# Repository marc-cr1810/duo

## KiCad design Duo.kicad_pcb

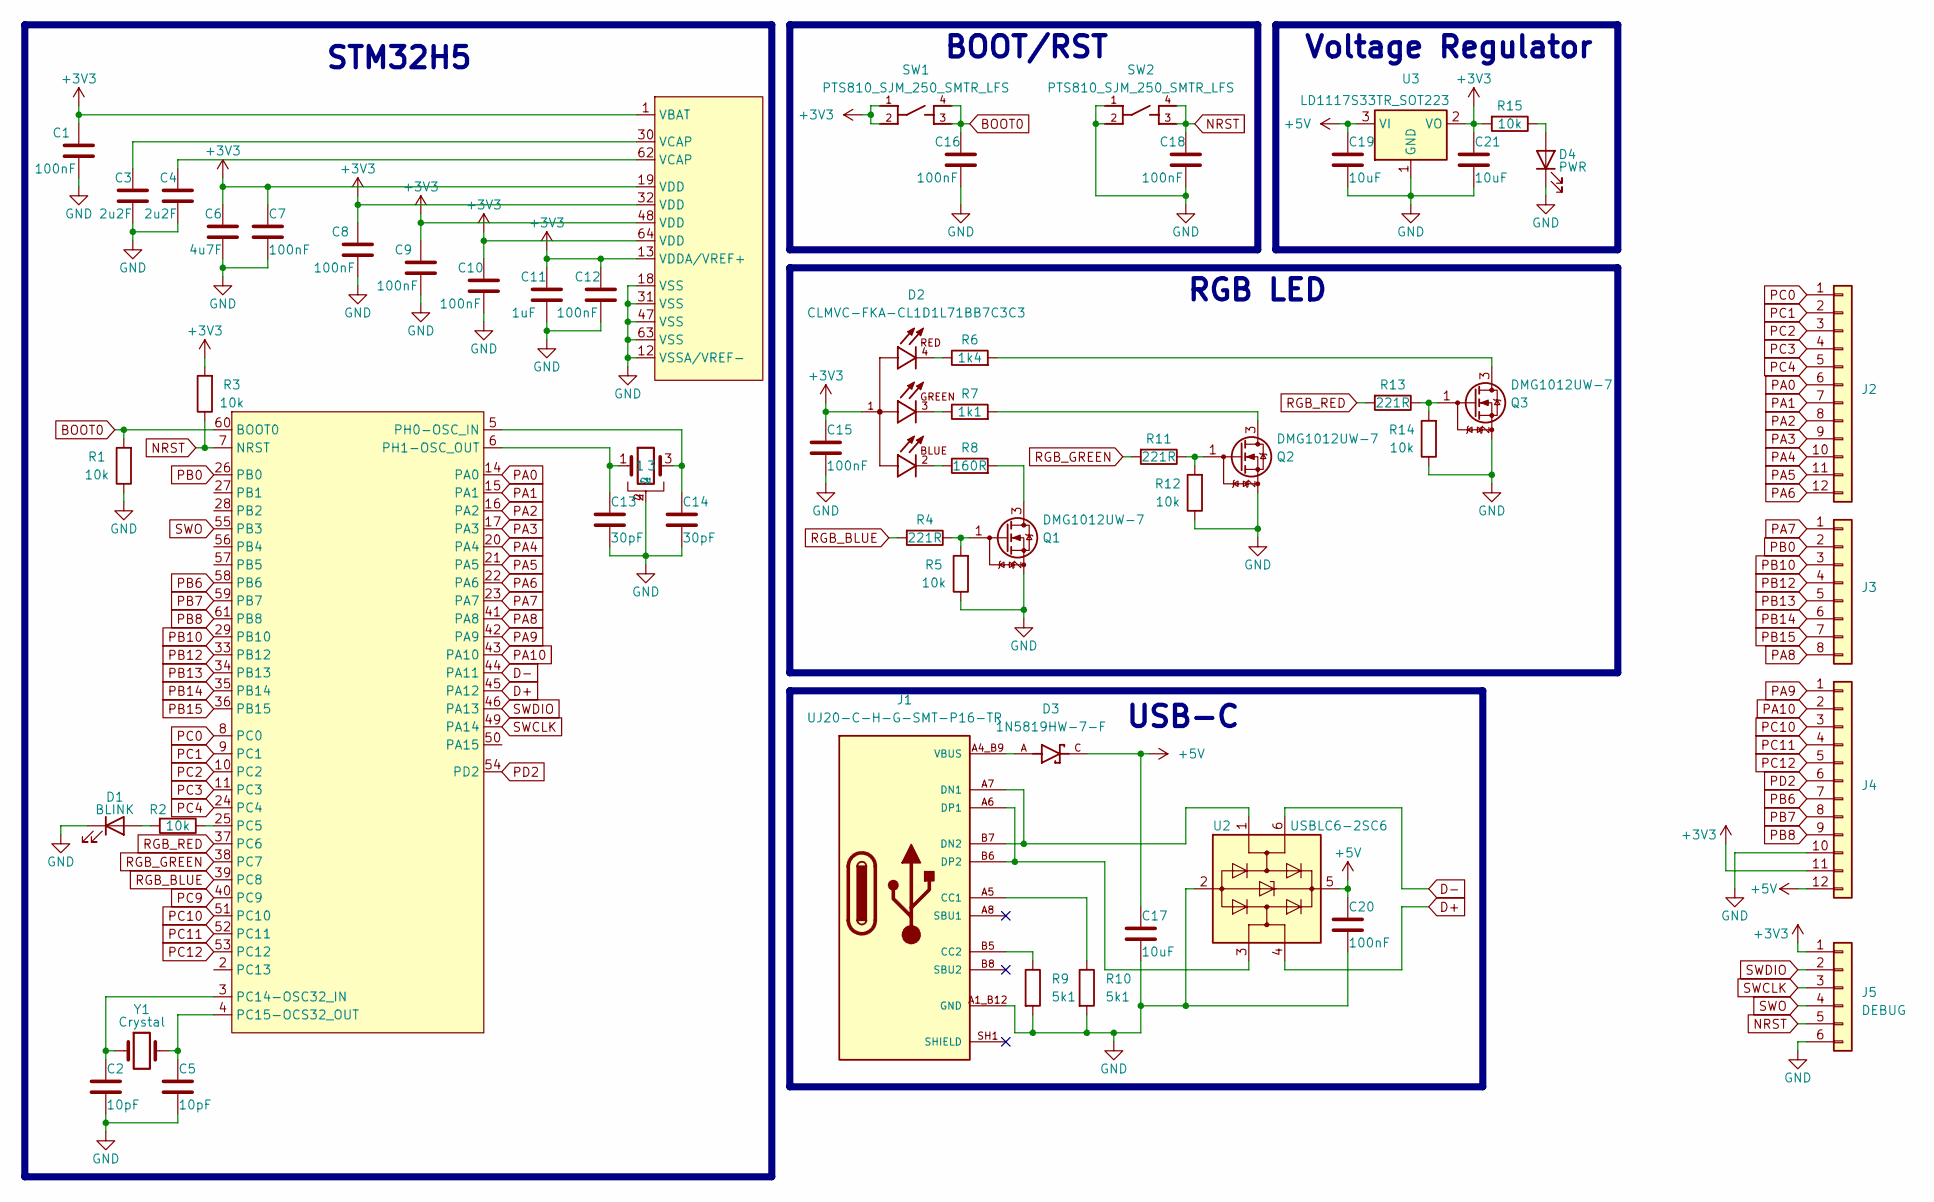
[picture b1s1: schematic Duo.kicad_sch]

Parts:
C1, C7, C8, C9, C10, C12, C15, C16, C18, C20: 100nF; C_0402_1005Metric; Part Number CL05B104KA5NNNC
C2, C5: 10pF; C_0402_1005Metric; Part Number CC0402JRNPO9BN100
C3, C4: 2u2F; C_0603_1608Metric; Part Number CL10A225KO8NNNC
C6: 4u7F; C_0603_1608Metric; Part Number CL10A475KO8NNNC
C11: 1uF; C_0402_1005Metric; Part Number GRM155R61E105KA12D
C13, C14: 30pF; C_0402_1005Metric; Part Number CC0402JRNPO9BN300
C17, C19, C21: 10uF; C_0603_1608Metric; Part Number CL10A106KP8NNNC
D1: BLINK; LED_0603_1608Metric
D2: CLMVC-FKA-CL1D1L71BB7C3C3; LED_CLMVC-FKA-CL1D1L71BB7C3C3; PARTREV 14; DigiKey_Part_Number CLMVC-FKA-CL1D1L71BB7C3C3CT-ND
D3: 1N5819HW-7-F; SOD3715X145N; Part Number 1N5819HW-7-F
D4: PWR; LED_0603_1608Metric
J1: UJ20-C-H-G-SMT-P16-TR; SAMESKY_UJ20-C-H-G-SMT-P16-TR; PARTREV 1.0; DigiKey_Part_Number 2223-UJ20-C-H-G-SMT-P16-TRCT-ND
J2, J4: PinHeader-Castellated-12
J3: PinHeader-Castellated-8
J5: DEBUG; PinHeader_1x06_P2.54mm_Vertical
Q1, Q2, Q3: DMG1012UW-7; SOT-323_SC-70; Part Number DMG1012UW-7
R1, R2, R3, R5, R12, R14, R15: 10k; R_0402_1005Metric; Part Number AC0402FR-0710KL
R4, R11, R13: 221R; R_0402_1005Metric; Part Number RC0402FR-07221RL
R6: 1k4; R_0402_1005Metric; Part Number RC0402FR-071K4L
R7: 1k1; R_0402_1005Metric; Part Number RC0402FR-071K1L
R8: 160R; R_0402_1005Metric; Part Number RC0402FR-07160RL
R9, R10: 5k1; R_0402_1005Metric; Part Number RC0402FR-075K1L
SW1, SW2: PTS810_SJM_250_SMTR_LFS; SW_PTS810_SJM_250_SMTR_LFS; Part Number PTS810SJG250SMTR LFS
U1: STM32H573RITx; LQFP-64_10x10mm_P0.5mm
U2: USBLC6-2SC6; SOT-23-6; Part Number USBLC6-2SC6
U3: LD1117S33TR_SOT223; SOT-223-3_TabPin2
Y1: Crystal; Crystal_SMD_MicroCrystal_CC7V-T1A-2Pin_3.2x1.5mm
Y2: ECS-80-18-23B-JTN-TR; XTAL_ECS-80-18-23B-JTN-TR; DigiKey_Part_Number XC3083CT-ND

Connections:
+3V3: C1.1, C6.2, C7.1, C8.1, C9.1, C10.1, C11.1, C12.1, C15.1, C21.1, D2.1, J4.11, J5.1, R3.2, R15.2, SW1.1, SW1.2, U1.1 (VBAT), U1.13 (VDDA/VREF+), U1.19 (VDD), U1.32 (VDD), U1.48 (VDD), U1.64 (VDD), U3.2 (VO)
+5V: C17.1, C19.1, C20.1, D3.C, J4.12, U2.5 (VBUS), U3.3 (VI)
BOOT0: C16.1, R1.2, SW1.3, SW1.4, U1.60 (BOOT0)
D+: U1.45 (PA12), U2.4 (I/O2)
D-: U1.44 (PA11), U2.6 (I/O1)
GND: C1.2, C2.2, C3.1, C4.1, C5.2, C6.1, C7.2, C8.2, C9.2, C10.2, C11.2, C12.2, C13.2, C14.2, C15.2, C16.2, C17.2, C18.2, C19.2, C20.2, C21.2, D1.1 (K), D4.1 (K), J1.A1_B12 (GND), J1.A12_B1 (GND), J4.10, J5.6, Q1.2 (S), Q2.2 (S), Q3.2 (S), R1.1, R5.1, R9.2, R10.2, R12.1, R14.1, SW2.1, SW2.2, U1.12 (VSSA/VREF-), U1.18 (VSS), U1.31 (VSS), U1.47 (VSS), U1.63 (VSS), U2.2 (GND), U3.1 (GND), Y2.2, Y2.4
NRST: C18.1, J5.5, R3.1, SW2.3, SW2.4, U1.7 (NRST)
unnamed: C3.2, U1.30 (VCAP)
unnamed: C4.2, U1.62 (VCAP)
unnamed: D1.2 (A), R2.2
unnamed: D2.2, R8.1
unnamed: D2.3, R7.1
unnamed: D2.4, R6.1
unnamed: D4.2 (A), R15.1
unnamed: J1.A5 (CC1), R10.1
unnamed: J1.B5 (CC2), R9.1
unnamed: J1.A7 (DN1), J1.B7 (DN2), U2.1 (I/O1)
unnamed: J1.A6 (DP1), J1.B6 (DP2), U2.3 (I/O2)
unnamed: Q1.3 (D), R8.2
unnamed: Q1.1 (G), R4.1, R5.2
unnamed: Q2.3 (D), R7.2
unnamed: Q2.1 (G), R11.1, R12.2
unnamed: Q3.3 (D), R6.2
unnamed: Q3.1 (G), R13.1, R14.2
unnamed: R2.1, U1.25 (PC5)
unnamed: C2.1, U1.3 (PC14-OSC32_IN), Y1.1
unnamed: C5.1, U1.4 (PC15-OCS32_OUT), Y1.2
unnamed: C14.1, U1.5 (PH0-OSC_IN), Y2.3
unnamed: C13.1, U1.6 (PH1-OSC_OUT), Y2.1
PA0: J2.6, U1.14 (PA0)
PA1: J2.7, U1.15 (PA1)
PA2: J2.8, U1.16 (PA2)
PA3: J2.9, U1.17 (PA3)
PA4: J2.10, U1.20 (PA4)
PA5: J2.11, U1.21 (PA5)
PA6: J2.12, U1.22 (PA6)
PA7: J3.1, U1.23 (PA7)
PA8: J3.8, U1.41 (PA8)
PA9: J4.1, U1.42 (PA9)
PA10: J4.2, U1.43 (PA10)
PB0: J3.2, U1.26 (PB0)
PB6: J4.7, U1.58 (PB6)
PB7: J4.8, U1.59 (PB7)
PB8: J4.9, U1.61 (PB8)
PB10: J3.3, U1.29 (PB10)
PB12: J3.4, U1.33 (PB12)
PB13: J3.5, U1.34 (PB13)
PB14: J3.6, U1.35 (PB14)
PB15: J3.7, U1.36 (PB15)
PC0: J2.1, U1.8 (PC0)
PC1: J2.2, U1.9 (PC1)
PC2: J2.3, U1.10 (PC2)
PC3: J2.4, U1.11 (PC3)
PC4: J2.5, U1.24 (PC4)
PC9: U1.40 (PC9)
PC10: J4.3, U1.51 (PC10)
PC11: J4.4, U1.52 (PC11)
PC12: J4.5, U1.53 (PC12)
PD2: J4.6, U1.54 (PD2)
RGB_BLUE: R4.2, U1.39 (PC8)
RGB_GREEN: R11.2, U1.38 (PC7)
RGB_RED: R13.2, U1.37 (PC6)
SWCLK: J5.3, U1.49 (PA14)
SWDIO: J5.2, U1.46 (PA13)
SWO: J5.4, U1.55 (PB3)
VBUS: D3.A, J1.A4_B9 (VBUS), J1.A9_B4 (VBUS)

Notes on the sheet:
BOOT/RST
STM32H5
Voltage Regulator
USB-C
RGB LED

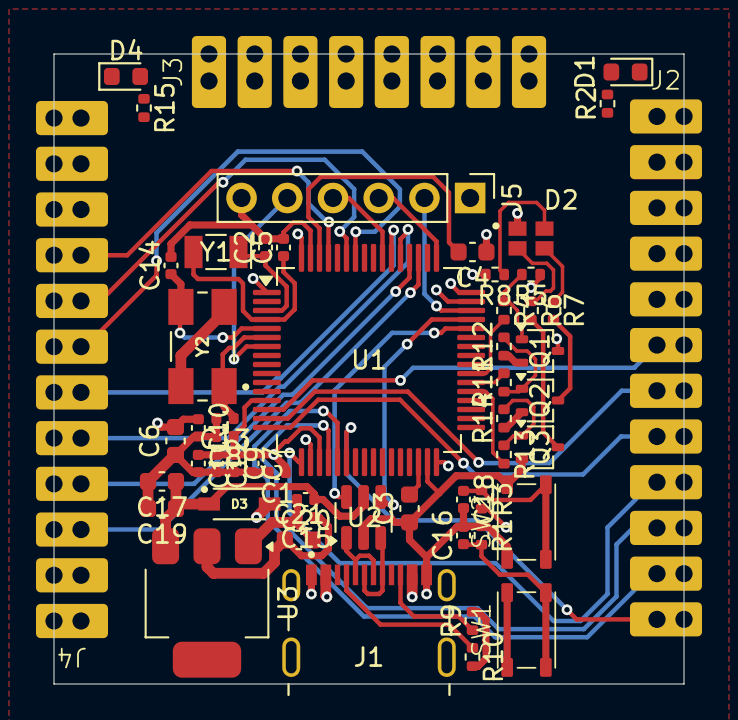
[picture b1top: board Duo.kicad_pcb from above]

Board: 4 copper layers, 35.0 x 35.0 mm, 55 parts (0 on the bottom side), 65 nets.
